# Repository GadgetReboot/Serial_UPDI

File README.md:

# Serial_UPDI
<br><br><BR><BR>
Serial UPDI Programmer

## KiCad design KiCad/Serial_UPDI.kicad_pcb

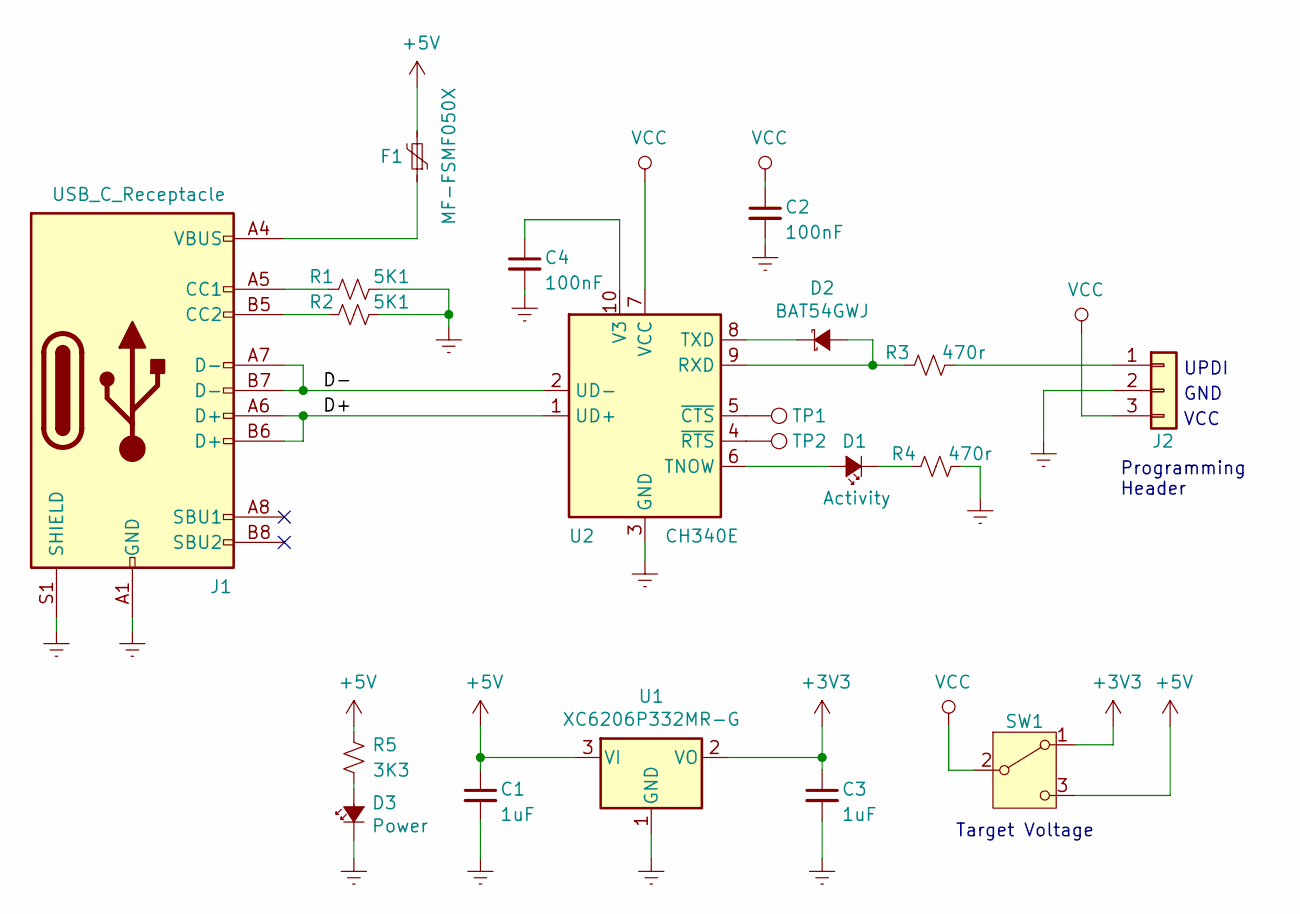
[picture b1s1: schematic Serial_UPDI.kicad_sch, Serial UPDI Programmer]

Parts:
C1, C3: 1uF; C_0805_2012Metric_Pad1.15x1.40mm_HandSolder
C2, C4: 100nF; C_0805_2012Metric_Pad1.15x1.40mm_HandSolder
D1: Activity; LED_0805_2012Metric_Pad1.15x1.40mm_HandSolder
D2: BAT54GWJ; SOD-123
D3: Power; LED_0805_2012Metric_Pad1.15x1.40mm_HandSolder
F1: MF-FSMF050X; R_0603_1608Metric_Pad1.05x0.95mm_HandSolder
J1: USB_C_Receptacle; USB_C_Receptacle_XKB_U262-16XN-4BVC11; Part # XKB Connectivity U262-161N-4BVC11
J2: Conn_01x03; PinHeader_1x03_P2.54mm_Vertical
R1, R2: 5K1; R_0805_2012Metric_Pad1.15x1.40mm_HandSolder
R3, R4: 470r; R_0805_2012Metric_Pad1.15x1.40mm_HandSolder
R5: 3K3; R_0805_2012Metric_Pad1.15x1.40mm_HandSolder
SW1: SW_SPDT; SW_SPDT_PCM12_
TP1, TP2: TestPoint; TestPoint_Loop_D1.80mm_Drill1.0mm_Beaded
U1: XC6206P332MR-G; SOT-23
U2: CH340E; MSOP-10_3x3mm_P0.5mm

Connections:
+3V3: C3.1, SW1.1 (A), U1.2 (VO)
+5V: C1.1, F1.2, R5.1, SW1.3 (C), U1.3 (VI)
/D+: J1.A6 (D+), J1.B6 (D+), U2.1 (UD+)
/D-: J1.A7 (D-), J1.B7 (D-), U2.2 (UD-)
GNDREF: C1.2, C2.2, C3.2, C4.2, D3.1 (K), J1.A1 (GND), J1.A12 (GND), J1.B1 (GND), J1.B12 (GND), J1.S1 (SHIELD), J2.2, R1.1, R2.1, R4.1, U1.1 (GND), U2.3 (GND)
unnamed: C4.1, U2.10 (V3)
unnamed: D1.1 (K), R4.2
unnamed: D1.2 (A), U2.6 (TNOW)
unnamed: D2.1 (K), U2.8 (TXD)
unnamed: D2.2 (A), R3.2, U2.9 (RXD)
unnamed: D3.2 (A), R5.2
unnamed: F1.1, J1.A4 (VBUS), J1.A9 (VBUS), J1.B4 (VBUS), J1.B9 (VBUS)
unnamed: J1.A5 (CC1), R1.2
unnamed: J1.B5 (CC2), R2.2
unnamed: J2.1, R3.1
unnamed: TP1.1, U2.5 (~CTS)
unnamed: TP2.1, U2.4 (~RTS)
VCC: C2.1, J2.3, SW1.2 (B), U2.7 (VCC)

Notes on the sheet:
GND
Programming Header
Target Voltage
UPDI
VCC

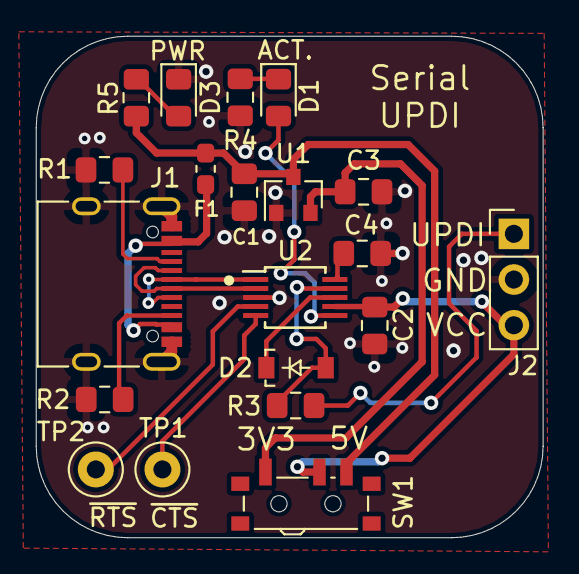
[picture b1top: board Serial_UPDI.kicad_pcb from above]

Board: 2 copper layers, 28.2 x 27.9 mm, 20 parts (0 on the bottom side), 18 nets.
